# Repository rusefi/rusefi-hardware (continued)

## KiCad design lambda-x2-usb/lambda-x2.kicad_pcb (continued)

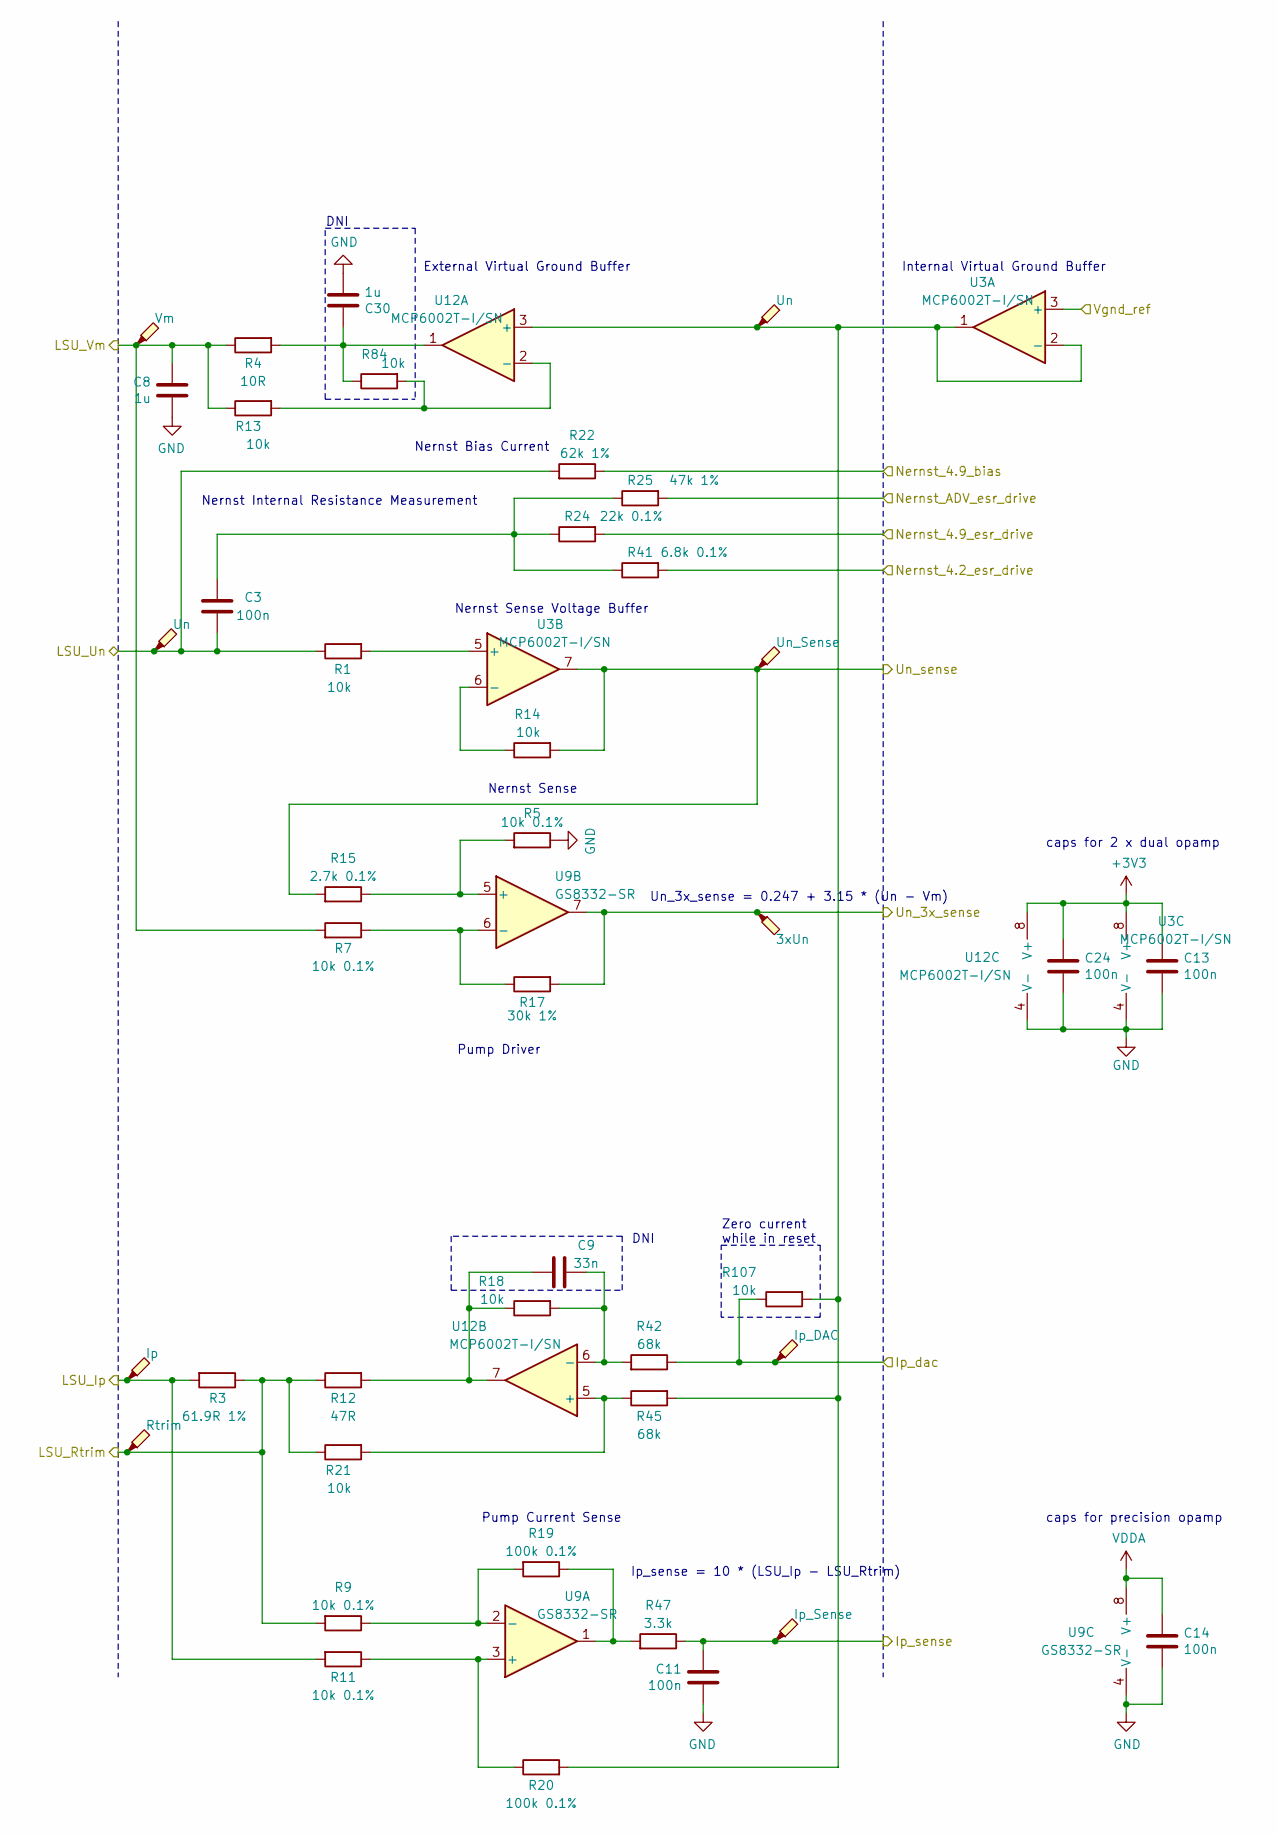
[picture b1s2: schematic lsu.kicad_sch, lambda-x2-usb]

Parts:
C3, C11, C13, C14, C24: 100n; C_0402_1005Metric; LCSC C1525
C8, C30: 1u; C_0402_1005Metric; LCSC C52923
C9: 33n; C_0402_1005Metric; LCSC C1585
R1, R13, R14, R18, R21, R84, R107: 10k; R_0402_1005Metric; LCSC C25744
R3: 61.9R 1%; R_0805_2012Metric; LCSC C322537
R4: 10R; R_1206_3216Metric; LCSC C17903
R5, R7, R9, R11: 10k 0.1%; R_0603_1608Metric; LCSC C309083
R12: 47R; R_0603_1608Metric; LCSC C114623
R15: 2.7k 0.1%; R_0603_1608Metric; LCSC C318131
R17: 30k 1%; R_0603_1608Metric; LCSC C22984
R19, R20: 100k 0.1%; R_0603_1608Metric; LCSC C122538
R22: 62k 1%; R_0603_1608Metric; LCSC C23221
R24: 22k 0.1%; R_0603_1608Metric; LCSC C705830
R25: 47k 1%; R_0603_1608Metric; LCSC C25819
R41: 6.8k 0.1%; R_0603_1608Metric; LCSC C705876
R42, R45: 68k; R_0402_1005Metric; LCSC C36871
R47: 3.3k; R_0402_1005Metric; LCSC C25890
TP3: Un_Sense; TestPoint_Pad_D1.0mm
TP5: 3xUn; TestPoint_Pad_D1.0mm
TP10: Ip; TestPoint_Pad_D1.0mm
TP11: Rtrim; TestPoint_Pad_D1.0mm
TP12: Vm; TestPoint_Pad_D1.0mm
TP13, TP14: Un; TestPoint_Pad_D1.0mm
TP15: Ip_DAC; TestPoint_Pad_D1.0mm
TP16: Ip_Sense; TestPoint_Pad_D1.0mm
U3, U12: MCP6002T-I/SN; SOIC-8_3.9x4.9mm_P1.27mm; LCSC C7377
U9: GS8332-SR; SOIC-8_3.9x4.9mm_P1.27mm; LCSC C157713

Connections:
+3V3: C13.1, C24.1, U3.8 (V+), U12.8 (V+); also elsewhere on the board
/LSU analog left/Un_sense: R14.2, R15.2, TP3.1 (1_1), U3.7; also elsewhere on the board
/LSU analog left/Vgnd_ref: U3.3 (+); also elsewhere on the board
/L_Ip_dac: R42.1, R107.1, TP15.1 (1_1); also elsewhere on the board
/L_Ip_sense: C11.1, R47.1, TP16.1 (1_1); also elsewhere on the board
/L_LSU_Ip: R3.2, R11.2, TP10.1 (1_1); also elsewhere on the board
/L_LSU_Rtrim: R3.1, R9.2, R12.1, R21.1, TP11.1 (1_1); also elsewhere on the board
/L_LSU_Un: C3.1, R1.1, R22.2, TP13.1 (1_1); also elsewhere on the board
/L_LSU_Vm: C8.1, R4.1, R7.2, R13.1, TP12.1 (1_1); also elsewhere on the board
/L_Nernst_4.2_esr_drive: R41.2; also elsewhere on the board
/L_Nernst_4.9_bias: R22.1; also elsewhere on the board
/L_Nernst_4.9_esr_drive: R24.2; also elsewhere on the board
/L_Nernst_ADV_esr_drive: R25.2; also elsewhere on the board
/L_Un_3x_sense: R17.2, TP5.1 (1_1), U9.7; also elsewhere on the board
GND: C8.2, C11.2, C13.2, C14.2, C24.2, C30.2, R5.1, U3.4 (V-), U9.4 (V-), U12.4 (V-); also elsewhere on the board
unnamed: C3.2, R24.1, R25.1, R41.1
unnamed: C9.1, R12.2, R18.1, U12.7
unnamed: C30.1, R4.2, R84.1, U12.1
unnamed: R19.1, R47.2, U9.1
unnamed: R1.2, U3.5 (+)
unnamed: R14.1, U3.6 (-)
unnamed: R11.1, R20.1, U9.3 (+)
unnamed: R9.1, R19.2, U9.2 (-)
unnamed: R5.2, R15.1, U9.5 (+)
unnamed: R7.1, R17.1, U9.6 (-)
unnamed: R20.2, R45.2, R107.2, TP14.1 (1_1), U3.1, U3.2 (-), U12.3 (+)
unnamed: R13.2, R84.2, U12.2 (-)
unnamed: R21.2, R45.1, U12.5 (+)
unnamed: C9.2, R18.2, R42.2, U12.6 (-)
VDDA: C14.1, U9.8 (V+); also elsewhere on the board

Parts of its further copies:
C15, C18, C20, C23, C29: 100n; C_0402_1005Metric; LCSC C1525
C16, C31: 1u; C_0402_1005Metric; LCSC C52923
C17: 33n; C_0402_1005Metric; LCSC C1585
R54, R62, R63, R66, R69, R85, R108: 10k; R_0402_1005Metric; LCSC C25744
R55: 61.9R 1%; R_0805_2012Metric; LCSC C322537
R56: 10R; R_1206_3216Metric; LCSC C17903
R57, R58, R59, R60: 10k 0.1%; R_0603_1608Metric; LCSC C309083
R61: 47R; R_0603_1608Metric; LCSC C114623
R64: 2.7k 0.1%; R_0603_1608Metric; LCSC C318131
R65: 30k 1%; R_0603_1608Metric; LCSC C22984
R67, R68: 100k 0.1%; R_0603_1608Metric; LCSC C122538
R70: 62k 1%; R_0603_1608Metric; LCSC C23221
R71: 22k 0.1%; R_0603_1608Metric; LCSC C705830
R72: 47k 1%; R_0603_1608Metric; LCSC C25819
R73: 6.8k 0.1%; R_0603_1608Metric; LCSC C705876
R74, R75: 68k; R_0402_1005Metric; LCSC C36871
R77: 3.3k; R_0402_1005Metric; LCSC C25890
TP4: Un_Sense; TestPoint_Pad_D1.0mm
TP6: 3xUn; TestPoint_Pad_D1.0mm
TP17: Ip; TestPoint_Pad_D1.0mm
TP18: Rtrim; TestPoint_Pad_D1.0mm
TP19: Vm; TestPoint_Pad_D1.0mm
TP20, TP21: Un; TestPoint_Pad_D1.0mm
TP22: Ip_DAC; TestPoint_Pad_D1.0mm
TP23: Ip_Sense; TestPoint_Pad_D1.0mm
U10, U13: MCP6002T-I/SN; SOIC-8_3.9x4.9mm_P1.27mm; LCSC C7377
U11: GS8332-SR; SOIC-8_3.9x4.9mm_P1.27mm; LCSC C157713

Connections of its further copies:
+3V3: C20.1, C29.1, U10.8 (V+), U13.8 (V+); also elsewhere on the board
/LSU analog left/Vgnd_ref: U10.3 (+); also elsewhere on the board
/LSU analog right/Un_sense: R63.2, R64.2, TP4.1 (1_1), U10.7; also elsewhere on the board
/R_Ip_dac: R74.1, R108.1, TP22.1 (1_1); also elsewhere on the board
/R_Ip_sense: C18.1, R77.1, TP23.1 (1_1); also elsewhere on the board
/R_LSU_Ip: R55.2, R60.2, TP17.1 (1_1); also elsewhere on the board
/R_LSU_Rtrim: R55.1, R59.2, R61.1, R69.1, TP18.1 (1_1); also elsewhere on the board
/R_LSU_Un: C15.1, R54.1, R70.2, TP20.1 (1_1); also elsewhere on the board
/R_LSU_Vm: C16.1, R56.1, R58.2, R62.1, TP19.1 (1_1); also elsewhere on the board
/R_Nernst_4.2_esr_drive: R73.2; also elsewhere on the board
/R_Nernst_4.9_bias: R70.1; also elsewhere on the board
/R_Nernst_4.9_esr_drive: R71.2; also elsewhere on the board
/R_Nernst_ADV_esr_drive: R72.2; also elsewhere on the board
/R_Un_3x_sense: R65.2, TP6.1 (1_1), U11.7; also elsewhere on the board
GND: C16.2, C18.2, C20.2, C23.2, C29.2, C31.2, R57.1, U10.4 (V-), U11.4 (V-), U13.4 (V-); also elsewhere on the board
unnamed: C15.2, R71.1, R72.1, R73.1
unnamed: C17.1, R61.2, R66.1, U13.7
unnamed: C31.1, R56.2, R85.1, U13.1
unnamed: R67.1, R77.2, U11.1
unnamed: R68.2, R75.2, R108.2, TP21.1 (1_1), U10.1, U10.2 (-), U13.3 (+)
unnamed: R54.2, U10.5 (+)
unnamed: R63.1, U10.6 (-)
unnamed: R60.1, R68.1, U11.3 (+)
unnamed: R59.1, R67.2, U11.2 (-)
unnamed: R57.2, R64.1, U11.5 (+)
unnamed: R58.1, R65.1, U11.6 (-)
unnamed: R62.2, R85.2, U13.2 (-)
unnamed: R69.2, R75.1, U13.5 (+)
unnamed: C17.2, R66.2, R74.2, U13.6 (-)
VDDA: C23.1, U11.8 (V+); also elsewhere on the board

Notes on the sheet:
Nernst Sense Voltage Buffer
Ip_sense = 10 * (LSU_Ip - LSU_Rtrim)
caps for 2 x dual opamp
Nernst Sense
Nernst Bias Current
DNI
Pump Current Sense
External Virtual Ground Buffer
Internal Virtual Ground Buffer
Un_3x_sense = 0.247 + 3.15 * (Un - Vm)
Pump Driver
Nernst Internal Resistance Measurement
Zero current while in reset
caps for precision opamp

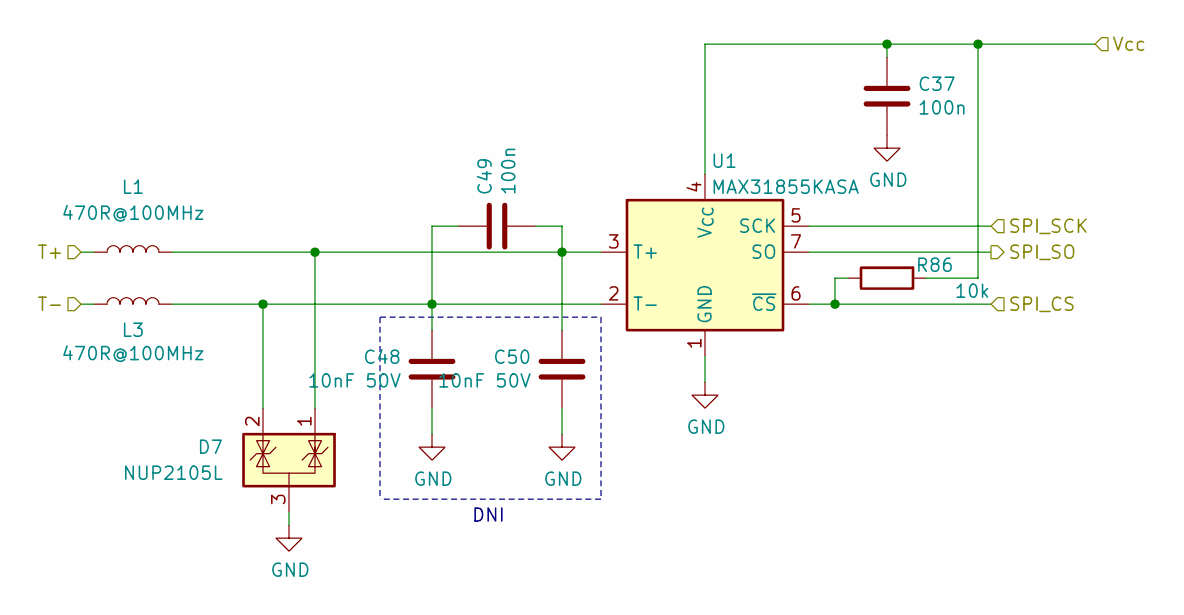
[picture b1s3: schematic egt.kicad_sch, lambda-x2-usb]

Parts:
C37, C49: 100n; C_0402_1005Metric; LCSC C1525
C48, C50: 10nF 50V; C_0402_1005Metric; LCSC C1524
D7: NUP2105L; SOT-23; LCSC C284104
L1, L3: 470R@100MHz; L_0603_1608Metric; LCSC C97853
R86: 10k; R_0402_1005Metric; LCSC C25744
U1: MAX31855KASA; SOIC-8_3.9x4.9mm_P1.27mm; LCSC C52028

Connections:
+3V3: C37.1, R86.2, U1.4 (V_{CC}); also elsewhere on the board
/L_EGT+: L1.1; also elsewhere on the board
/L_EGT-: L3.1; also elsewhere on the board
/SPI1_CS0: R86.1, U1.6 (~CS); also elsewhere on the board
/SPI1_MISO: U1.7 (SO); also elsewhere on the board
/SPI1_SCK: U1.5 (SCK); also elsewhere on the board
GND: C37.2, C48.2, C50.2, D7.3 (A), U1.1 (GND); also elsewhere on the board
unnamed: C49.2, C50.1, D7.1 (K), L1.2, U1.3 (T+)
unnamed: C48.1, C49.1, D7.2 (K), L3.2, U1.2 (T-)

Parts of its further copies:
C12, C51, C53, C58, C61, C63, C66, C68, C76, C82, C85, C87, C90, C92: 10nF 50V; C_0402_1005Metric; LCSC C1524
C19, C46, C52, C59, C62, C64, C67, C69, C81, C83, C86, C88, C91, C93: 100n; C_0402_1005Metric; LCSC C1525
D21, D22, D23, D24, D25, D26, D27: NUP2105L; SOT-23; LCSC C284104
L2, L4, L6, L7, L8, L9, L10, L11, L12, L13, L14, L15, L16, L17: 470R@100MHz; L_0603_1608Metric; LCSC C97853
R87, R88, R89, R90, R91, R92, R93: 10k; R_0402_1005Metric; LCSC C25744
U14, U15, U16, U18, U19, U20, U21: MAX31855KASA; SOIC-8_3.9x4.9mm_P1.27mm; LCSC C52028

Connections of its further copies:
+3V3: C46.1, C59.1, C64.1, C69.1, C83.1, C88.1, C93.1, R87.2, R88.2, R89.2, R90.2, R91.2, R92.2, R93.2, U14.4 (V_{CC}), U15.4 (V_{CC}), U16.4 (V_{CC}), U18.4 (V_{CC}), U19.4 (V_{CC}), U20.4 (V_{CC}), U21.4 (V_{CC}); also elsewhere on the board
/L2_EGT+: L6.1; also elsewhere on the board
/L2_EGT-: L7.1; also elsewhere on the board
/L3_EGT+: L8.1; also elsewhere on the board
/L3_EGT-: L9.1; also elsewhere on the board
/L4_EGT+: L10.1; also elsewhere on the board
/L4_EGT-: L11.1; also elsewhere on the board
/R2_EGT+: L12.1; also elsewhere on the board
/R2_EGT-: L13.1; also elsewhere on the board
/R3_EGT+: L14.1; also elsewhere on the board
/R3_EGT-: L15.1; also elsewhere on the board
/R4_EGT+: L16.1; also elsewhere on the board
/R4_EGT-: L17.1; also elsewhere on the board
/R_EGT+: L2.1; also elsewhere on the board
/R_EGT-: L4.1; also elsewhere on the board
/SPI1_CS1: R87.1, U14.6 (~CS); also elsewhere on the board
/SPI1_CS2: R88.1, U15.6 (~CS); also elsewhere on the board
/SPI1_CS3: R91.1, U19.6 (~CS); also elsewhere on the board
/SPI1_CS4: R89.1, U16.6 (~CS); also elsewhere on the board
/SPI1_CS5: R92.1, U20.6 (~CS); also elsewhere on the board
/SPI1_CS6: R90.1, U18.6 (~CS); also elsewhere on the board
/SPI1_CS7: R93.1, U21.6 (~CS); also elsewhere on the board
/SPI1_MISO: U14.7 (SO), U15.7 (SO), U16.7 (SO), U18.7 (SO), U19.7 (SO), U20.7 (SO), U21.7 (SO); also elsewhere on the board
/SPI1_SCK: U14.5 (SCK), U15.5 (SCK), U16.5 (SCK), U18.5 (SCK), U19.5 (SCK), U20.5 (SCK), U21.5 (SCK); also elsewhere on the board
GND: C12.2, C46.2, C51.2, C53.2, C58.2, C59.2, C61.2, C63.2, C64.2, C66.2, C68.2, C69.2, C76.2, C82.2, C83.2, C85.2, C87.2, C88.2, C90.2, C92.2, C93.2, D21.3 (A), D22.3 (A), D23.3 (A), D24.3 (A), D25.3 (A), D26.3 (A), D27.3 (A), U14.1 (GND), U15.1 (GND), U16.1 (GND), U18.1 (GND), U19.1 (GND), U20.1 (GND), U21.1 (GND); also elsewhere on the board
unnamed: C52.2, C53.1, D21.1 (K), L2.2, U14.3 (T+)
unnamed: C51.1, C52.1, D21.2 (K), L4.2, U14.2 (T-)
unnamed: C19.2, C58.1, D22.1 (K), L6.2, U15.3 (T+)
unnamed: C12.1, C19.1, D22.2 (K), L7.2, U15.2 (T-)
unnamed: C62.2, C63.1, D23.1 (K), L8.2, U16.3 (T+)
unnamed: C61.1, C62.1, D23.2 (K), L9.2, U16.2 (T-)
unnamed: C67.2, C68.1, D24.1 (K), L10.2, U18.3 (T+)
unnamed: C66.1, C67.1, D24.2 (K), L11.2, U18.2 (T-)
unnamed: C81.2, C82.1, D25.1 (K), L12.2, U19.3 (T+)
unnamed: C76.1, C81.1, D25.2 (K), L13.2, U19.2 (T-)
unnamed: C86.2, C87.1, D26.1 (K), L14.2, U20.3 (T+)
unnamed: C85.1, C86.1, D26.2 (K), L15.2, U20.2 (T-)
unnamed: C91.2, C92.1, D27.1 (K), L16.2, U21.3 (T+)
unnamed: C90.1, C91.1, D27.2 (K), L17.2, U21.2 (T-)

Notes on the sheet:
DNI

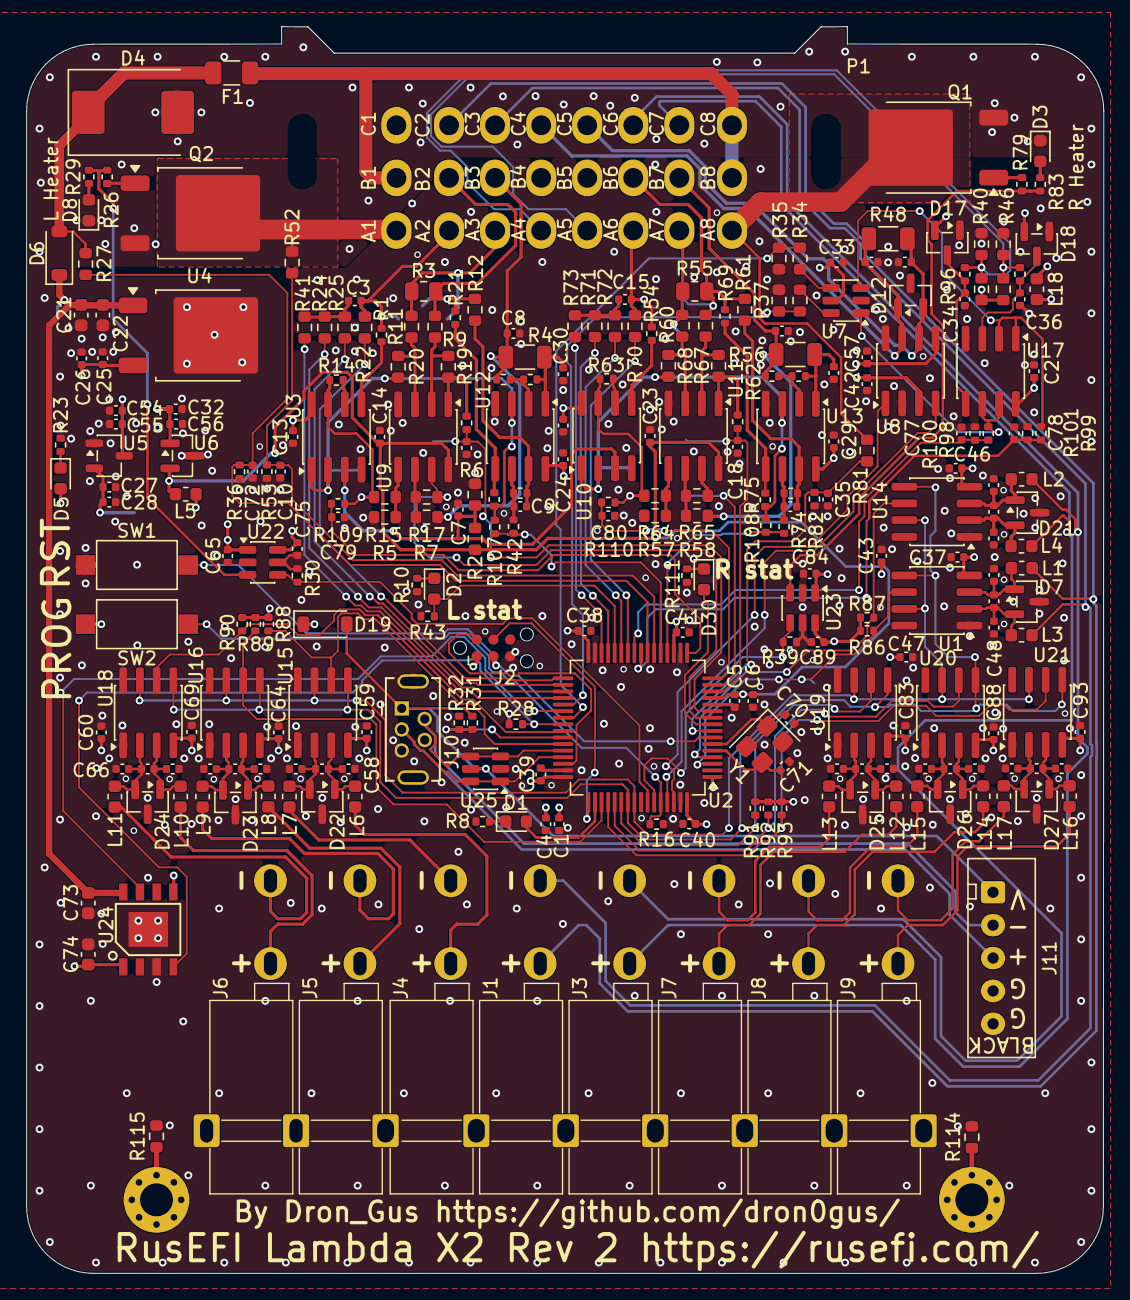
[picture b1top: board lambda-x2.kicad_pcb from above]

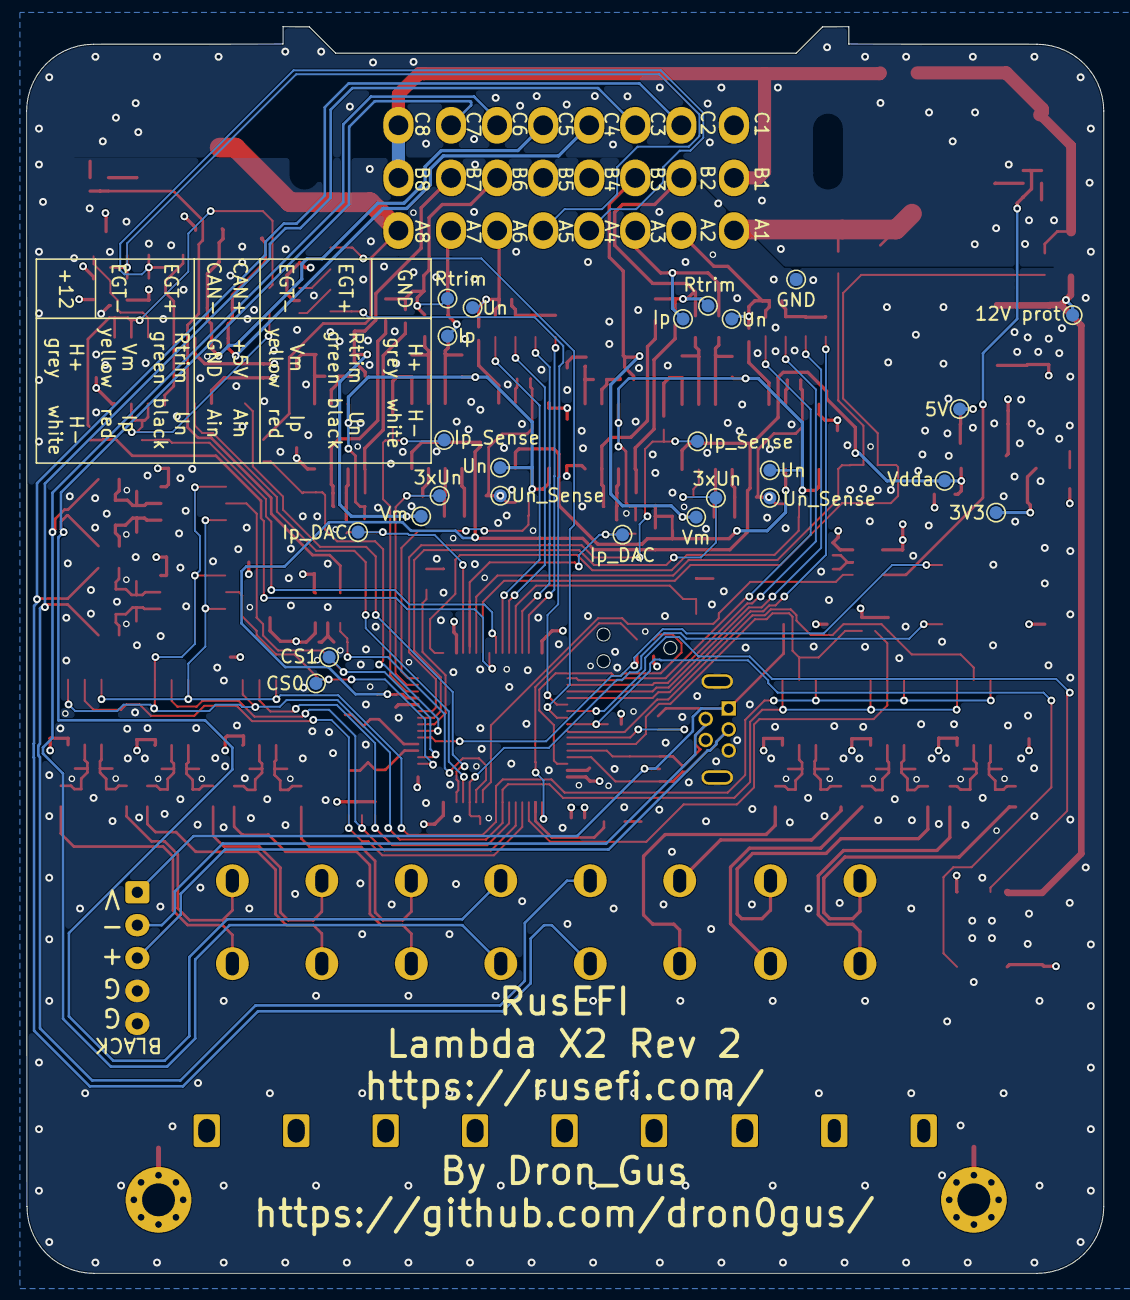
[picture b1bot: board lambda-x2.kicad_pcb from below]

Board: 4 copper layers, 81.9 x 94.8 mm, 301 parts (25 on the bottom side), 155 nets.

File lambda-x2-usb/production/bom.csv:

Designator,Footprint,Quantity,Value,LCSC Part #
"C1, C16, C25, C28, C32, C43, C47, C54, C6, C60, C7, C8",0402,12,1u,C52923
"C10, C34, C35, C36, C72, C77, C78, C79, C80",0402,9,1n,C106205
"C11, C13, C14, C15, C18, C19, C2, C20, C23, C24, C26, C27, C29, C3, C33, C37, C38, C39, C40, C41, C42, C46, C49, C5, C52, C55, C56, C57, C59, C62, C64, C65, C67, C69, C75, C81, C83, C84, C86, C88, C89, C91, C93",0402,43,100n,C1525
C21,0603,1,1u,C15849
"C22, C73",0603,2,100n,C14663
C4,0402,1,4.7u,C23733
"C44, C45",0402,2,47p,C1567
"C70, C71",0402,2,20pF 50V,C107000
C74,0603,1,2.2u,C23630
D1,0603,1,LED,C497940
"D12, D21, D22, D23, D24, D25, D26, D27, D7",SOT-23,9,NUP2105L,C284104
"D17, D18",SOT-23,2,BAT54S,C47546
D19,D_SOD-123,1,B5819W,C8598
"D2, D30, D5",0603,3,LED,C965804
"D3, D8",0603,2,LED,C2286
D4,D_SMC,1,SMCJ22CA,C310038
D6,D_SOD-123,1,1N4148W,C81598
F1,1206,1,BSMD1206-025-33V,C2977524
J10,USB-MINI-B-VERTICAL,1,USB_B_Mini,C13453
J11,USBBF7,1,USBBF7,C17899327
"L1, L10, L11, L12, L13, L14, L15, L16, L17, L2, L3, L4, L6, L7, L8, L9",0603,16,470R@100MHz,C97853
P1,33311-24AW-2,1,33311-24AW-2,C5349068
"Q1, Q2",TO-252-2,2,BTS3028,C112639
"R1, R107, R108, R13, R14, R16, R18, R21, R28, R30, R36, R39, R43, R53, R54, R62, R63, R66, R69, R82, R86, R87, R88, R89, R90, R91, R92, R93, R96, R97",0402,30,10k,C25744
"R10, R109, R110, R111, R23, R26, R29, R79, R8, R83",0402,10,1k,C11702
"R100, R101",0402,2,160k,C409854
"R11, R2, R5, R57, R58, R59, R6, R60, R7, R9",0603,10,10k 0.1%,C309083
"R12, R61",0603,2,47R,C114623
"R15, R64",0603,2,2.7k 0.1%,C318131
"R17, R33, R34, R65",0603,4,30k 1%,C22984
"R19, R20, R67, R68",0603,4,100k 0.1%,C122538
"R22, R70",0603,2,62k 1%,C23221
"R24, R71",0603,2,22k 0.1%,C705830
"R25, R35, R37, R72",0603,4,47k 1%,C25819
"R27, R52, R81",0603,3,100k 1%,C25803
"R3, R55",0805,2,61.9R 1%,C322537
R31,0402,1,33k,C25779
R32,0402,1,82k,C4142
"R4, R56",1206,2,10R,C17903
"R41, R73",0603,2,6.8k 0.1%,C705876
"R42, R45, R74, R75",0402,4,68k,C36871
"R47, R77",0402,2,3.3k,C25890
"R50, R51",0603,2,1K,C21190
"R98, R99",0402,2,82k,C325373
"U1, U14",SOIC-8_3.9x4.9mm_P1.27mm,2,MAX31855KASA,C52028
"U10, U12, U13, U17, U3",SOIC-8_3.9x4.9mm_P1.27mm,5,MCP6002T-I/SN,C7377
"U11, U9",SOIC-8_3.9x4.9mm_P1.27mm,2,GS8332-SR,C157713
U2,LQFP-64_10x10mm_P0.5mm,1,STM32F105RCTx,C8345
"U22, U23",SOT-23-6,2,SN74LVC1T45DBV,C7843
U24,PG-DSO-8-43,1,TLS115,C3747428
U25,SOT-23-6,1,SRV05-4,C6454456
U4,TO-252-2,1,LM78M05_TO252,C58069
U5,SOT-23-3,1,XC6206P332MR,C5446
U6,SOT-23,1,REF3033,C36658
U7,SOT-23-6,1,74LVC2G17DBV,C10429
U8,SOIC-8_3.9x4.9mm_P1.27mm,1,TJA1051T-3,C38695
Y1,Crystal_SMD_3225-4Pin_3.2x2.5mm,1,XXDCELNANF-8MHZ,C367183

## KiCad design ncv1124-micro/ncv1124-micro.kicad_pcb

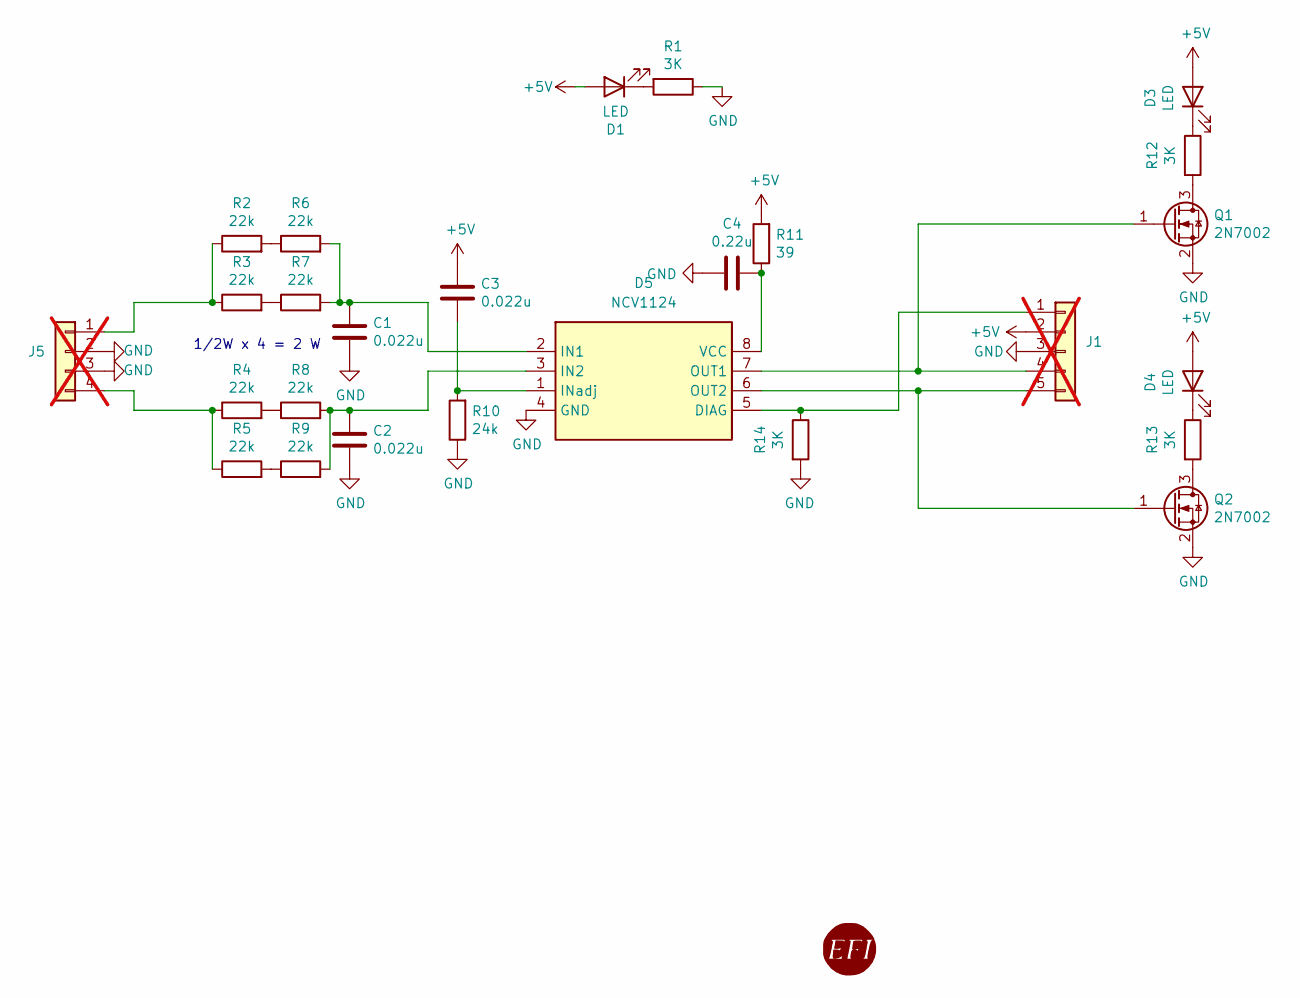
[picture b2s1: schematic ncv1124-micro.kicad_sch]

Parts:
C1, C2, C3: 0.022u; C_0603_1608Metric; LCSC C21122
C4: 0.22u; C_0603_1608Metric; LCSC C21120
D1, D3, D4: LED; LED_0603_1608Metric; LCSC C2290
D5: NCV1124; SO-8_3.9x4.9mm_P1.27mm; LCSC C152274
G1: RUSEFI_LOGO; rusefi_logo
J1: Conn_01x05; PinHeader_1x05_P2.54mm_Vertical; not fitted
J5: Conn_01x04; PinHeader_1x04_P2.54mm_Vertical; not fitted
Q1, Q2: 2N7002; SOT-23; LCSC C8545
R1, R12, R13, R14: 3K; R_0603_1608Metric; LCSC C4211
R2, R3, R4, R5, R6, R7, R8, R9: 22k; R_1210_3225Metric_Pad1.30x2.65mm_HandSolder; LCSC C230119
R10: 24k; R_0603_1608Metric; LCSC C23352
R11: 39; R_0603_1608Metric; LCSC C23154

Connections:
+5V: C3.1, D1.2 (A), D3.2 (A), D4.2 (A), J1.2, R11.2
GND: C1.2, C2.2, C4.2, D5.4 (GND), J1.3, J5.2, J5.3, Q1.2 (S), Q2.2 (S), R1.1, R10.1, R14.2
unnamed: D1.1 (K), R1.2
unnamed: D3.1 (K), R12.1
unnamed: D4.1 (K), R13.1
unnamed: D5.5 (DIAG), J1.1, R14.1
unnamed: C1.1, D5.2 (IN1), R6.2, R7.2
unnamed: C2.1, D5.3 (IN2), R8.2, R9.2
unnamed: C3.2, D5.1 (INadj), R10.2
unnamed: D5.7 (OUT1), J1.4, Q1.1 (G)
unnamed: D5.6 (OUT2), J1.5, Q2.1 (G)
unnamed: C4.1, D5.8 (VCC), R11.1
unnamed: J5.1, R2.1, R3.1
unnamed: J5.4, R4.1, R5.1
unnamed: Q1.3 (D), R12.2
unnamed: Q2.3 (D), R13.2
unnamed: R2.2, R6.1
unnamed: R3.2, R7.1
unnamed: R4.2, R8.1
unnamed: R5.2, R9.1

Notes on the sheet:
1/2W x 4 = 2 W

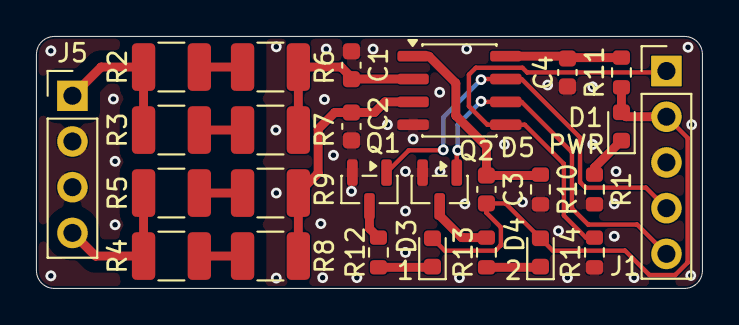
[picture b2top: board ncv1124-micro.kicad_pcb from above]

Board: 2 copper layers, 37.0 x 14.0 mm, 27 parts (1 on the bottom side), 20 nets.

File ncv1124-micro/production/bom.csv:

Designator,Footprint,Quantity,Value,LCSC Part #
"C1, C2, C3",0603,3,0.022u,C21122
C4,0603,1,0.22u,C21120
"D1, D3, D4",0603,3,LED,C2290
D5,SO-8_3.9x4.9mm_P1.27mm,1,NCV1124,C152274
"Q1, Q2",SOT-23,2,2N7002,C8545
"R1, R12, R13, R14",0603,4,3K,C4211
R10,0603,1,24k,C23352
R11,0603,1,39,C23154
"R2, R3, R4, R5, R6, R7, R8, R9",1210,8,22k,C230119

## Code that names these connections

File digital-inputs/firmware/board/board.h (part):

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/*
 * GPIOA setup:
 *
 * PA0  - ZIO_D32 TIM2_CH1          (input pullup).
 * PA1  - RMII_REF_CLK              (alternate 11).
 * PA2  - RMII_MDIO                 (alternate 11).
 * PA3  - ARD_A0 ADC123_IN3         (input pullup).
 * PA4  - ZIO_D24 SPI3_NSS          (input pullup).
 * PA5  - ARD_D13 SPI1_SCK          (input pullup).
 * PA6  - ARD_D12 SPI1_MISO         (input pullup).
 * PA7  - ARD_D11 SPI1_MOSI ZIO_D71 RMII_RX_DV(alternate 11).
 * PA8  - USB_SOF                   (alternate 10).
 * PA9  - USB_VBUS                  (analog).
 * PA10 - USB_ID                    (alternate 10).
 * PA11 - USB_DM                    (alternate 10).
 * PA12 - USB_DP                    (alternate 10).
 * PA13 - SWDIO                     (alternate 0).
 * PA14 - SWCLK                     (alternate 0).
 * PA15 - ZIO_D20 I2S3_WS           (input pullup).
 */
#define VAL_GPIOA_MODER             (PIN_MODE_INPUT(GPIOA_ZIO_D32) |        \
                                     PIN_MODE_ALTERNATE(GPIOA_RMII_REF_CLK) |\
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/*
 * GPIOB setup:
 *
 * PB0  - ZIO_D33 TIM3_CH3 LED1     (output pushpull maximum).
 * PB1  - ZIO_A6 ADC12_IN9          (input pullup).
 * PB2  - ZIO_D27                   (input pullup).
 * PB3  - ZIO_D23 I2S3_CK           (input pullup).
 * PB4  - ZIO_D25 SPI3_MISO         (input pullup).
 * PB5  - ZIO_D22 I2S3_SD           (input pullup).
 * PB6  - ZIO_D26                   (input pullup).
 * PB7  - LED2                      (output pushpull maximum).
 * PB8  - ARD_D15 I2C1_SCL          (input pullup).
 * PB9  - ARD_D14 I2C1_SDA          (input pullup).
 * PB10 - ZIO_D36 TIM2_CH3          (input pullup).
 * PB11 - ZIO_D35 TIM2_CH4          (input pullup).
 * PB12 - ZIO_D19 I2S2_WS           (input pullup).
 * PB13 - ZIO_D18 I2S2_CK RMII_TXD1 (alternate 11).
 * PB14 - LED3                      (output pushpull maximum).
 * PB15 - ZIO_D17 I2S2_SD           (input pullup).
 */
#define VAL_GPIOB_MODER             (PIN_MODE_OUTPUT(GPIOB_ZIO_D33) |       \
                                     PIN_MODE_INPUT(GPIOB_ZIO_A6) |         \
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/*
 * GPIOC setup:
 *
 * PC0  - ARD_A1 ADC123_IN10        (input pullup).
 * PC1  - RMII_MDC                  (alternate 11).
 * PC2  - ZIO_A7 ADC123_IN12        (input pullup).
 * PC3  - ARD_A2 ADC123_IN13        (input pullup).
 * PC4  - RMII_RXD0                 (alternate 11).
 * PC5  - RMII_RXD1                 (alternate 11).
 * PC6  - ZIO_D16 I2S2_MCK          (input pullup).
 * PC7  - ZIO_D21 I2S3_MCK          (input pullup).
 * PC8  - ZIO_D43 SDMMC_D0          (input pullup).
 * PC9  - ZIO_D44 SDMMC_D1          (input pullup).
 * PC10 - ZIO_D45 SDMMC_D2          (input pullup).
 * PC11 - ZIO_D46 SDMMC_D3          (input pullup).
 * PC12 - ZIO_D47 SDMMC_CK          (input pullup).
 * PC13 - BUTTON                    (input floating).
 * PC14 - OSC32_IN                  (input floating).
 * PC15 - OSC32_OUT                 (input floating).
 */
#define VAL_GPIOC_MODER             (PIN_MODE_INPUT(GPIOC_ARD_A1) |         \
                                     PIN_MODE_ALTERNATE(GPIOC_RMII_MDC) |   \
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/*
 * GPIOD setup:
 *
 * PD0  - ZIO_D67 CAN1_RX           (input pullup).
 * PD1  - ZIO_D66 CAN1_TX           (input pullup).
 * PD2  - ZIO_D48 SDMMC_CMD         (input pullup).
 * PD3  - ZIO_D55 USART2_CTS        (input pullup).
 * PD4  - ZIO_D54 USART2_RTS        (input pullup).
 * PD5  - ZIO_D53 USART2_TX         (input pullup).
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 * PE4  - ZIO_D57 SAI1_FS_A         (input pullup).
 * PE5  - ZIO_D58 SAI1_SCK_A        (input pullup).
 * PE6  - ZIO_D59 SAI1_SD_A         (input pullup).
 * PE7  - ZIO_D41 TIM1_ETR          (input pullup).
 * PE8  - ZIO_D42 TIM1_CH1N         (input pullup).
 * PE9  - ARD_D6 TIM1_CH1           (input pullup).
 * PE10 - ZIO_D40 TIM1_CH2N         (input pullup).
 * PE11 - ARD_D5 TIM1_CH2           (input pullup).
 * PE12 - ZIO_D39 TIM1_CH3N         (input pullup).
 * PE13 - ARD_D3 TIM1_CH3           (input pullup).
 * PE14 - ZIO_D38                   (input pullup).
 * PE15 - ZIO_D37 TIM1_BKIN1        (input pullup).
 */
#define VAL_GPIOE_MODER             (PIN_MODE_INPUT(GPIOE_ZIO_D34) |        \
                                     PIN_MODE_INPUT(GPIOE_PIN1) |           \
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/*
 * GPIOF setup:
 *
 * PF0  - ZIO_D68 I2C2_SDA          (input pullup).
 * PF1  - ZIO_D69 I2C2_SCL          (input pullup).
 * PF2  - ZIO_D70 I2C2_SMBA         (input pullup).
 * PF3  - ARD_A3 ADC3_IN9           (input pullup).
 * PF4  - ZIO_A8 ADC3_IN14          (input pullup).
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 * PG7  - USB_GPIO_IN               (input pullup).
 * PG8  - PIN8                      (input pullup).
 * PG9  - ARD_D0 USART6_RX          (input pullup).
 * PG10 - PIN10                     (input pullup).
 * PG11 - RMII_TX_EN                (alternate 11).
 * PG12 - PIN12                     (input pullup).
 * PG13 - RMII_TXD0                 (alternate 11).
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
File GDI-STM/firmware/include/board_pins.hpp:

#ifndef BOARD_PINS_HPP
#define BOARD_PINS_HPP

#include "stm32g4xx_hal.h"

#include <cstddef>
#include <cstdint>

namespace board {

struct GpioPin {
    GPIO_TypeDef* port;
    uint16_t pin;
};

// From `GDI-STM.kicad_pcb` (U7: STM32G474M, LQFP-80) - produced PCB is source of truth.
inline constexpr size_t kNumInjectors = 8;

// INJ1..INJ8 -> PE8..PE15 (LQFP80 pins 31..38).
inline constexpr GpioPin kInjPins[kNumInjectors] = {
    {GPIOE, GPIO_PIN_8},  // INJ1
    {GPIOE, GPIO_PIN_9},  // INJ2
    {GPIOE, GPIO_PIN_10}, // INJ3
    {GPIOE, GPIO_PIN_11}, // INJ4
    {GPIOE, GPIO_PIN_12}, // INJ5
    {GPIOE, GPIO_PIN_13}, // INJ6
    {GPIOE, GPIO_PIN_14}, // INJ7
    {GPIOE, GPIO_PIN_15}, // INJ8
};

// START1..START8 -> PA9,PA10,PB3,PB4,PA15,PB5,PB6,PB9 (pins 57,58,72,73,65,74,75,78).
inline constexpr GpioPin kStartPins[kNumInjectors] = {
    {GPIOA, GPIO_PIN_9},  // START1
    {GPIOA, GPIO_PIN_10}, // START2
    {GPIOB, GPIO_PIN_3},  // START3
    {GPIOB, GPIO_PIN_4},  // START4
    {GPIOA, GPIO_PIN_15}, // START5
    {GPIOB, GPIO_PIN_5},  // START6
    {GPIOB, GPIO_PIN_6},  // START7
    {GPIOB, GPIO_PIN_9},  // START8
};

// FDCAN1: CAN_TX -> PA12 (pin 60), CAN_RX -> PA11 (pin 59).
inline constexpr GpioPin kCanTx = {GPIOA, GPIO_PIN_12}; // CAN_TX
inline constexpr GpioPin kCanRx = {GPIOA, GPIO_PIN_11}; // CAN_RX

// High-side sense/control nets
// From `bank.kicad_sch` these nets feed IRS21867S gate-driver inputs (HIN). The firmware treats them as
// digital control outputs and holds them LOW at boot for safety (drivers disabled).
inline constexpr GpioPin kHsVbat[4] = {
    {GPIOC, GPIO_PIN_6}, // HS_VBAT1 (pin 52)
    {GPIOC, GPIO_PIN_7}, // HS_VBAT2 (pin 53)
    {GPIOC, GPIO_PIN_8}, // HS_VBAT3 (pin 54)
    {GPIOC, GPIO_PIN_9}, // HS_VBAT4 (pin 55)
};

inline constexpr GpioPin kHsVboost[4] = {
    {GPIOC, GPIO_PIN_10}, // HS_VBOOST1 (pin 66)
    {GPIOC, GPIO_PIN_11}, // HS_VBOOST2 (pin 67)
    {GPIOC, GPIO_PIN_12}, // HS_VBOOST3 (pin 68)
    {GPIOC, GPIO_PIN_13}, // HS_VBOOST4 (pin 2)
};

// Boost driver PWM/control.
inline constexpr GpioPin kBoostPwm = {GPIOD, GPIO_PIN_0}; // BOOST_PWM (pin 69)

// Analog sense pins (configured as analog inputs by board init).
inline constexpr GpioPin kSenseVboost = {GPIOE, GPIO_PIN_7};   // Vboost (pin 30)
inline constexpr GpioPin kSenseVoboost = {GPIOA, GPIO_PIN_8};  // Voboost (pin 56)
inline constexpr GpioPin kSenseVo1 = {GPIOA, GPIO_PIN_2};      // Vo1 (pin 14)
inline constexpr GpioPin kSenseVo2 = {GPIOA, GPIO_PIN_6};      // Vo2 (pin 20)
inline constexpr GpioPin kSenseVo3 = {GPIOB, GPIO_PIN_1};      // Vo3 (pin 25)
inline constexpr GpioPin kSenseVo4 = {GPIOB, GPIO_PIN_12};     // Vo4 (pin 43)

inline constexpr GpioPin kSenseVinM1 = {GPIOC, GPIO_PIN_5};     // VinM1 (pin 23)
inline constexpr GpioPin kSenseVinM2 = {GPIOA, GPIO_PIN_5};     // VinM2 (pin 19)
inline constexpr GpioPin kSenseVinM3 = {GPIOB, GPIO_PIN_2};     // VinM3 (pin 26)
inline constexpr GpioPin kSenseVinM4 = {GPIOB, GPIO_PIN_10};    // VinM4 (pin 39)
inline constexpr GpioPin kSenseVinMboost = {GPIOB, GPIO_PIN_15}; // VinMboost (pin 46)

inline constexpr GpioPin kSenseVinP1 = {GPIOA, GPIO_PIN_7};      // VinP1 (pin 21)
inline constexpr GpioPin kSenseVinP2 = {GPIOB, GPIO_PIN_0};      // VinP2 (pin 24)
inline constexpr GpioPin kSenseVinP3 = {GPIOB, GPIO_PIN_13};     // VinP3 (pin 44)
inline constexpr GpioPin kSenseVinP4 = {GPIOB, GPIO_PIN_11};     // VinP4 (pin 42)
inline constexpr GpioPin kSenseVinPboost = {GPIOC, GPIO_PIN_3};  // VinPboost (pin 11)

inline constexpr GpioPin kSenseVinj1 = {GPIOC, GPIO_PIN_0}; // Vinj1 (pin 8)
inline constexpr GpioPin kSenseVinj2 = {GPIOC, GPIO_PIN_1}; // Vinj2 (pin 9)
inline constexpr GpioPin kSenseVinj3 = {GPIOC, GPIO_PIN_2}; // Vinj3 (pin 10)
inline constexpr GpioPin kSenseVinj4 = {GPIOA, GPIO_PIN_0}; // Vinj4 (pin 12)
inline constexpr GpioPin kSenseVinj5 = {GPIOA, GPIO_PIN_1}; // Vinj5 (pin 13)
inline constexpr GpioPin kSenseVinj6 = {GPIOA, GPIO_PIN_3}; // Vinj6 (pin 17)
inline constexpr GpioPin kSenseVinj7 = {GPIOA, GPIO_PIN_4}; // Vinj7 (pin 18)
inline constexpr GpioPin kSenseVinj8 = {GPIOC, GPIO_PIN_4}; // Vinj8 (pin 22)

} // namespace board

#endif // BOARD_PINS_HPP
